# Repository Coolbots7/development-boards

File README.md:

# Development Boards
PCBs made to test core designs and / or help with rapid prototyping.

# Boards
## ATMega32u4 Development Board (Arduino Micro Equivalent)
Breadboard breakout PCB for an ATMega32u4 8-bit AVR microcontroller.

### Features:
* USB-C connector for programming and power up to 250mA.
* 5V 500mA linear regulator for external power up to 12VDC.
* Power, TX, RX, and D13 LEDs.
* Pins are labeled on both the top and bottom of the board for easy reference.
  * Note: The pinout is not the same as an actual Arduino Micro

### Bill of Materials:
[Shopping Cart on DigiKey](https://www.digikey.com/short/4ch5mv)

### Future Ideas:
* Ability to construct 3.3V and 5V versions using the same PCB

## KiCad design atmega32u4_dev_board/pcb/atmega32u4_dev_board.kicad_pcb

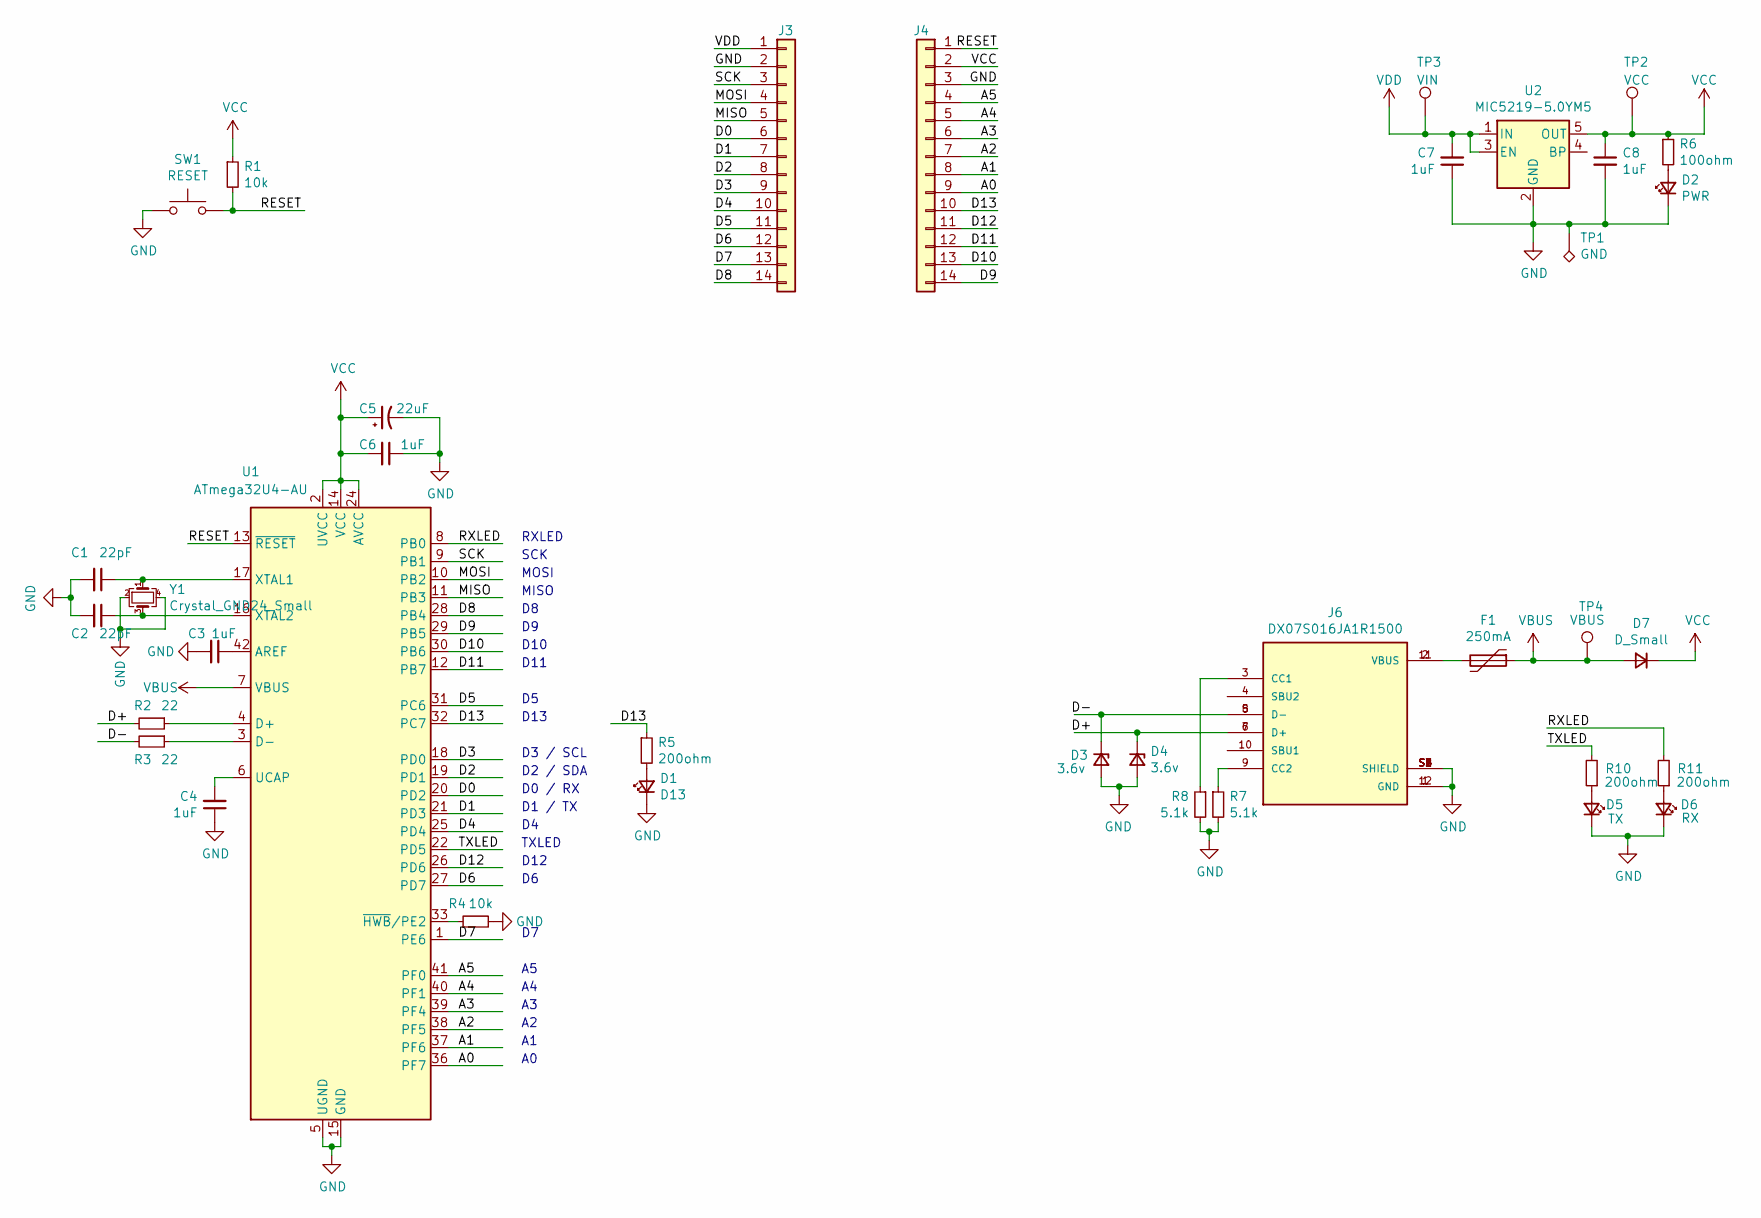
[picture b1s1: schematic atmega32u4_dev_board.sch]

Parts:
C1, C2: 22pF; C_0603_1608Metric
C3, C4, C6, C7, C8: 1uF; C_0603_1608Metric
C5: 22uF; C_0603_1608Metric
D1: D13; LED_0603_1608Metric
D2: PWR; LED_0603_1608Metric
D3, D4: 3.6v; D_0402_1005Metric
D5: TX; LED_0603_1608Metric
D6: RX; LED_0603_1608Metric
D7: D_Small; D_0603_1608Metric
F1: 250mA; Fuse_1206_3216Metric
J3, J4: Conn_01x14; PinHeader_1x14_P2.54mm_Vertical
J6: DX07S016JA1R1500; JAE_DX07S016JA1R1500; PARTREV 1
R1, R4: 10k; R_0603_1608Metric
R2, R3: 22; R_0603_1608Metric
R5, R10, R11: 200ohm; R_0603_1608Metric
R6: 100ohm; R_0603_1608Metric
R7, R8: 5.1k; R_0603_1608Metric
SW1: RESET; SW_SPST_B3U-1000P
TP1: GND; TestPoint_Pad_1.5x1.5mm
TP2: VCC; TestPoint_Pad_D1.5mm
TP3: VIN; TestPoint_Pad_D1.5mm
TP4: VBUS; TestPoint_Pad_D1.5mm
U1: ATmega32U4-AU; QFN-44-1EP_7x7mm_P0.5mm_EP5.2x5.2mm
U2: MIC5219-5.0YM5; SOT-23-5
Y1: Crystal_GND24_Small; Crystal_SMD_3225-4Pin_3.2x2.5mm

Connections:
/A0: J4.9, U1.36 (PF7)
/A1: J4.8, U1.37 (PF6)
/A2: J4.7, U1.38 (PF5)
/A3: J4.6, U1.39 (PF4)
/A4: J4.5, U1.40 (PF1)
/A5: J4.4, U1.41 (PF0)
/D0: J3.6, U1.20 (PD2)
/D1: J3.7, U1.21 (PD3)
/D2: J3.8, U1.19 (PD1)
/D3: J3.9, U1.18 (PD0)
/D4: J3.10, U1.25 (PD4)
/D5: J3.11, U1.31 (PC6)
/D6: J3.12, U1.27 (PD7)
/D7: J3.13, U1.1 (PE6)
/D8: J3.14, U1.28 (PB4)
/D9: J4.14, U1.29 (PB5)
/D10: J4.13, U1.30 (PB6)
/D11: J4.12, U1.12 (PB7)
/D12: J4.11, U1.26 (PD6)
/D13: J4.10, R5.1, U1.32 (PC7)
/D+: D4.1 (K), J6.6 (D+), J6.7 (D+), R2.2
/D-: D3.1 (K), J6.5 (D-), J6.8 (D-), R3.2
/MISO: J3.5, U1.11 (PB3)
/MOSI: J3.4, U1.10 (PB2)
/RESET: J4.1, R1.2, SW1.2, U1.13 (~RESET)
/RXLED: R11.2, U1.8 (PB0)
/SCK: J3.3, U1.9 (PB1)
/TXLED: R10.2, U1.22 (PD5)
GND: C1.2, C2.2, C3.2, C4.1, C5.2, C6.1, C7.1, C8.2, D1.1 (K), D2.1 (K), D3.2 (A), D4.2 (A), D5.1 (K), D6.1 (K), J3.2, J4.3, J6.1 (GND), J6.12 (GND), J6.S1 (SHIELD), J6.S2 (SHIELD), J6.S3 (SHIELD), J6.S4 (SHIELD), J6.S5 (SHIELD), J6.S6 (SHIELD), R4.2, R7.2, R8.2, SW1.1, TP1.1, U1.5 (UGND), U1.15 (GND), U1.23 (GND), U1.35 (GND), U1.43 (GND), U2.2 (GND), Y1.2, Y1.4
unnamed: C1.1, U1.17 (XTAL1), Y1.1
unnamed: C2.1, U1.16 (XTAL2), Y1.3
unnamed: C3.1, U1.42 (AREF)
unnamed: C4.2, U1.6 (UCAP)
unnamed: D1.2 (A), R5.2
unnamed: D2.2 (A), R6.2
unnamed: D5.2 (A), R10.1
unnamed: D6.2 (A), R11.1
unnamed: F1.2, J6.2 (VBUS), J6.11 (VBUS)
unnamed: J6.3 (CC1), R8.1
unnamed: J6.9 (CC2), R7.1
unnamed: R2.1, U1.4 (D+)
unnamed: R3.1, U1.3 (D-)
unnamed: R4.1, U1.33 (~HWB~/PE2)
VBUS: D7.2 (A), F1.1, TP4.1, U1.7 (VBUS)
VCC: C5.1, C6.2, C8.1, D7.1 (K), J4.2, R1.1, R6.1, TP2.1, U1.2 (UVCC), U1.14 (VCC), U1.24 (AVCC), U1.34 (VCC), U1.44 (AVCC), U2.5 (OUT)
VDD: C7.2, J3.1, TP3.1, U2.1 (IN), U2.3 (EN)

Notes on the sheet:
RXLED
SCK
MOSI
MISO
D3 / SCL
D2 / SDA
D0 / RX
D1 / TX
TXLED
D12
D10
D11
D13

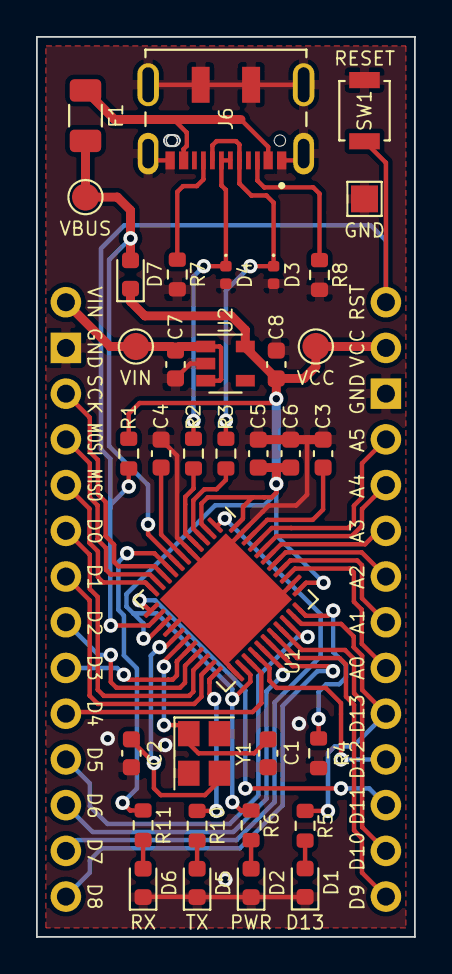
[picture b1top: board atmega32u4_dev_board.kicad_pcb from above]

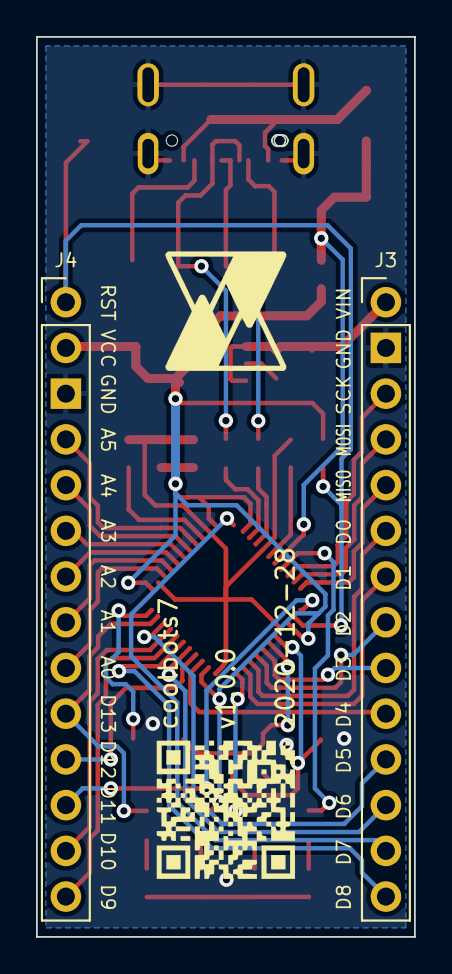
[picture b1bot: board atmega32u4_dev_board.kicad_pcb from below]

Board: 2 copper layers, 21.0 x 50.0 mm, 37 parts (2 on the bottom side), 46 nets.

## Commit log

2021-01-11 Initial Commit. README and KiCAD gitignore.
2021-01-12 Add repository qr code
2021-01-12 Add atmega32u4 dev board v1.0.0
